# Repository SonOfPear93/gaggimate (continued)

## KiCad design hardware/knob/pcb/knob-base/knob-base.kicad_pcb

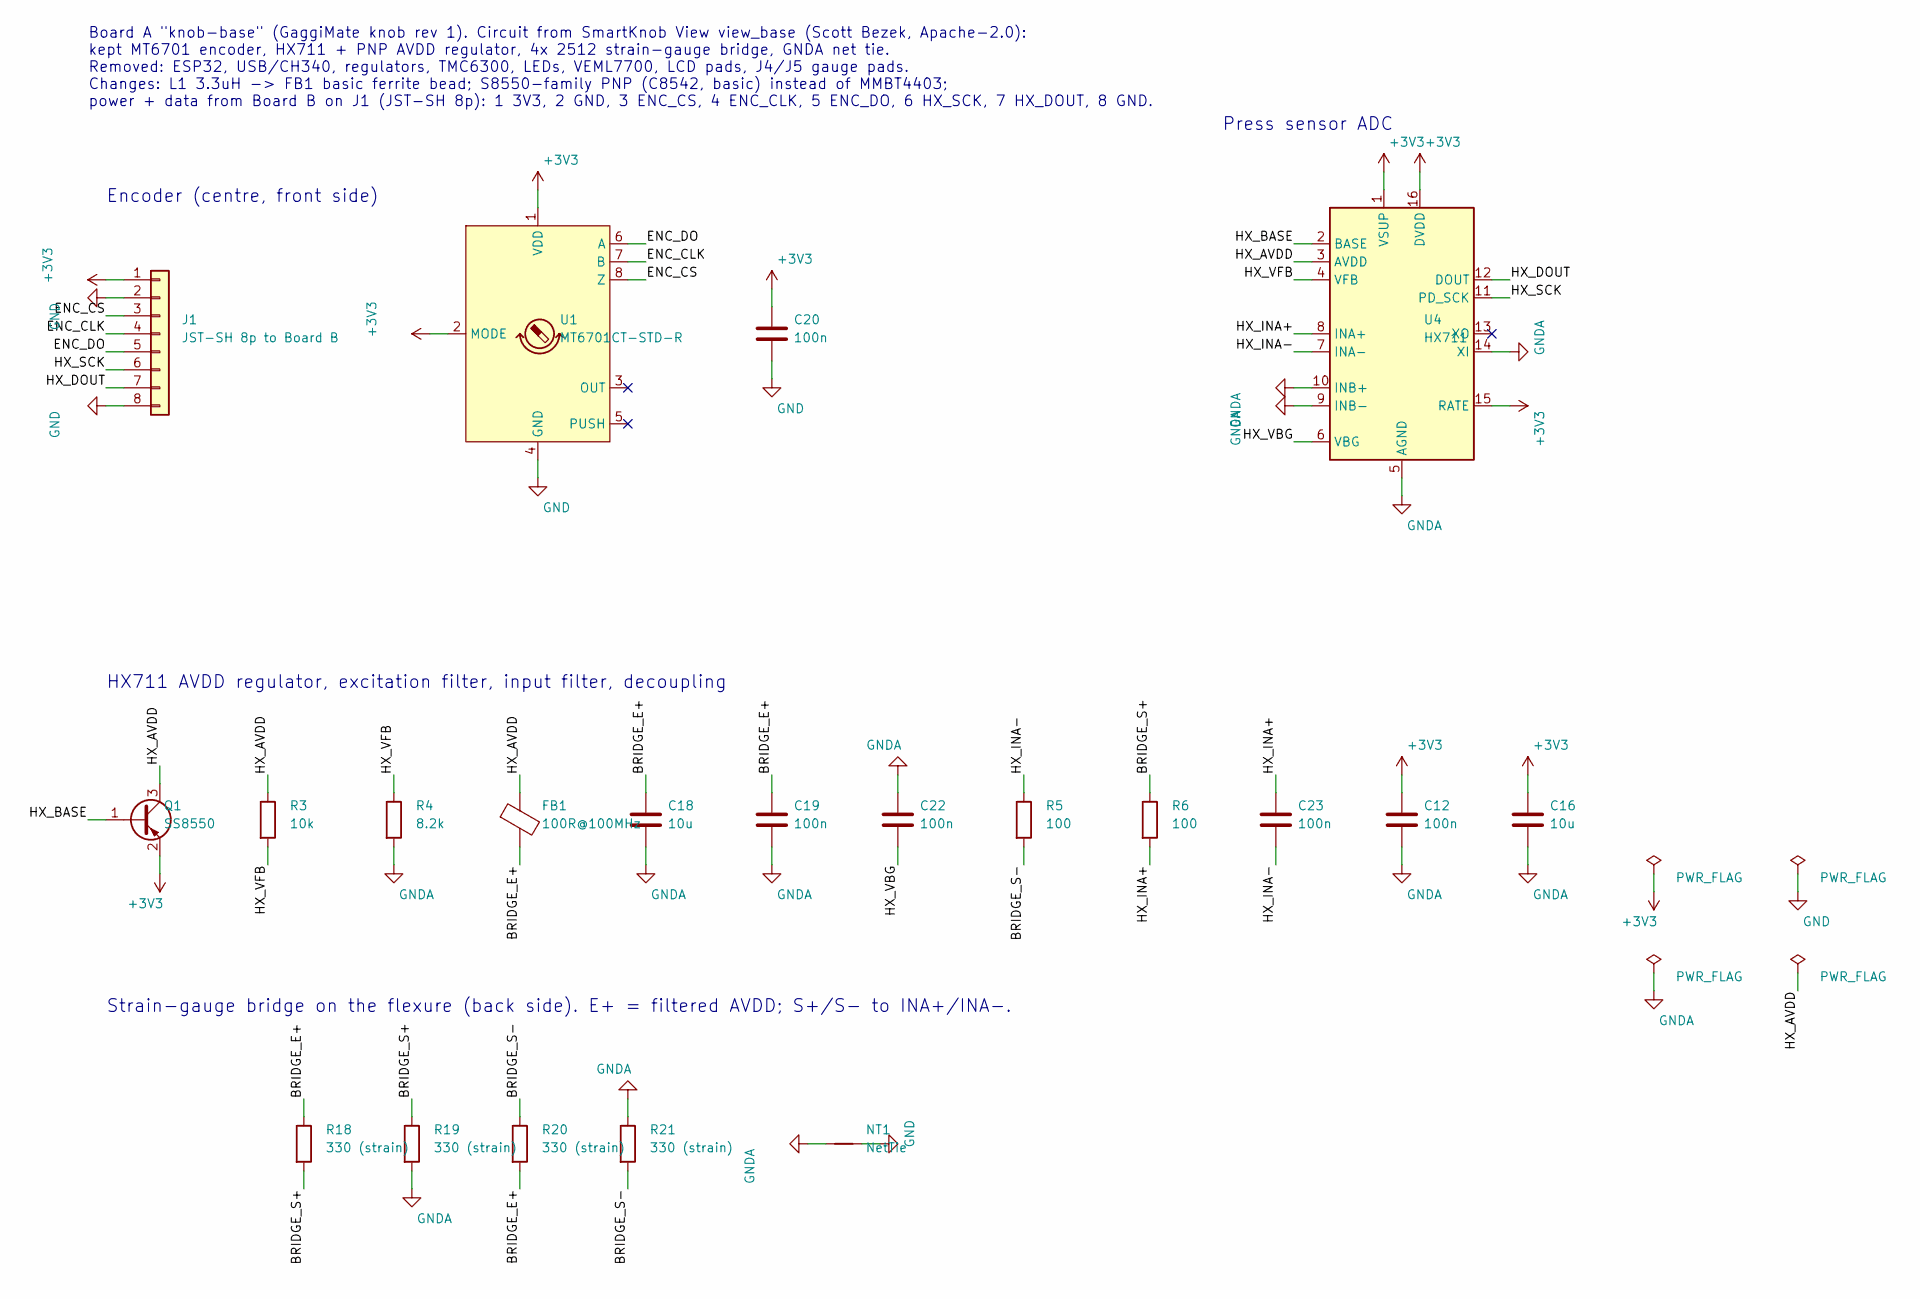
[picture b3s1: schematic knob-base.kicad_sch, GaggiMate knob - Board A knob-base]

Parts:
C12, C19, C20, C22, C23: 100n; C_0603_1608Metric; MPN CC0603KRX7R9BB104; LCSC C14663
C16, C18: 10u; C_0805_2012Metric; MPN CL21A106KAYNNNE; LCSC C15850
FB1: 100R@100MHz; L_0805_2012Metric; MPN GZ2012D101TF; LCSC C1015
J1: JST-SH 8p to Board B; JST_SH_SM08B-SRSS-TB_1x08-1MP_P1.00mm_Horizontal; MPN SM08B-SRSS-TB(LF)(SN); LCSC C160407
NT1: NetTie; NetTie-2_SMD_Pad0.5mm
Q1: SS8550; SOT-23; MPN SS8550 Y2; LCSC C8542
R3: 10k; R_0603_1608Metric; MPN 0603WAF1002T5E; LCSC C25804
R4: 8.2k; R_0603_1608Metric; MPN 0603WAF8201T5E; LCSC C25981
R5, R6: 100; R_0603_1608Metric; MPN 0603WAF1000T5E; LCSC C22775
R18, R19, R20, R21: 330 (strain); R_2512_6332Metric; MPN 25121WJ0331T4E; LCSC C19866
U1: MT6701CT-STD-R; SOIC-8_3.9x4.9mm_P1.27mm; MPN MT6701CT-STD-R; LCSC C3003196
U4: HX711; SOIC-16_3.9x9.9mm_P1.27mm; MPN HX711; LCSC C6705483

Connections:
+3V3: C12.1, C16.1, C20.1, J1.1, Q1.2 (E), U1.1 (VDD), U1.2 (MODE), U4.1 (VSUP), U4.15 (RATE), U4.16 (DVDD)
/BRIDGE_E+: C18.1, C19.1, FB1.2, R18.1, R20.2
/BRIDGE_S+: R6.1, R18.2, R19.1
/BRIDGE_S-: R5.2, R20.1, R21.2
/ENC_CLK: J1.4, U1.7 (B)
/ENC_CS: J1.3, U1.8 (Z)
/ENC_DO: J1.5, U1.6 (A)
/HX_AVDD: FB1.1, Q1.3 (C), R3.1, U4.3 (AVDD)
/HX_BASE: Q1.1 (B), U4.2 (BASE)
/HX_DOUT: J1.7, U4.12 (DOUT)
/HX_INA+: C23.1, R6.2, U4.8 (INA+)
/HX_INA-: C23.2, R5.1, U4.7 (INA-)
/HX_SCK: J1.6, U4.11 (PD_SCK)
/HX_VBG: C22.2, U4.6 (VBG)
/HX_VFB: R3.2, R4.1, U4.4 (VFB)
GND: C20.2, J1.2, J1.8, NT1.2, U1.4 (GND)
GNDA: C12.2, C16.2, C18.2, C19.2, C22.1, NT1.1, R4.2, R19.2, R21.1, U4.5 (AGND), U4.9 (INB-), U4.10 (INB+), U4.14 (XI)

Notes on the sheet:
Board A "knob-base" (GaggiMate knob rev 1). Circuit from SmartKnob View view_base (Scott Bezek, Apache-2.0): kept MT6701 encoder, HX711 + PNP AVDD regulator, 4x 2512 strain-gauge bridge, GNDA net tie. Removed: ESP32, USB/CH340, regulators, TMC6300, LEDs, VEML7700, LCD pads, J4/J5 gauge pads. Change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
Encoder (centre, front side)
Press sensor ADC
HX711 AVDD regulator, excitation filter, input filter, decoupling
Strain-gauge bridge on the flexure (back side). E+ = filtered AVDD; S+/S- to INA+/INA-.

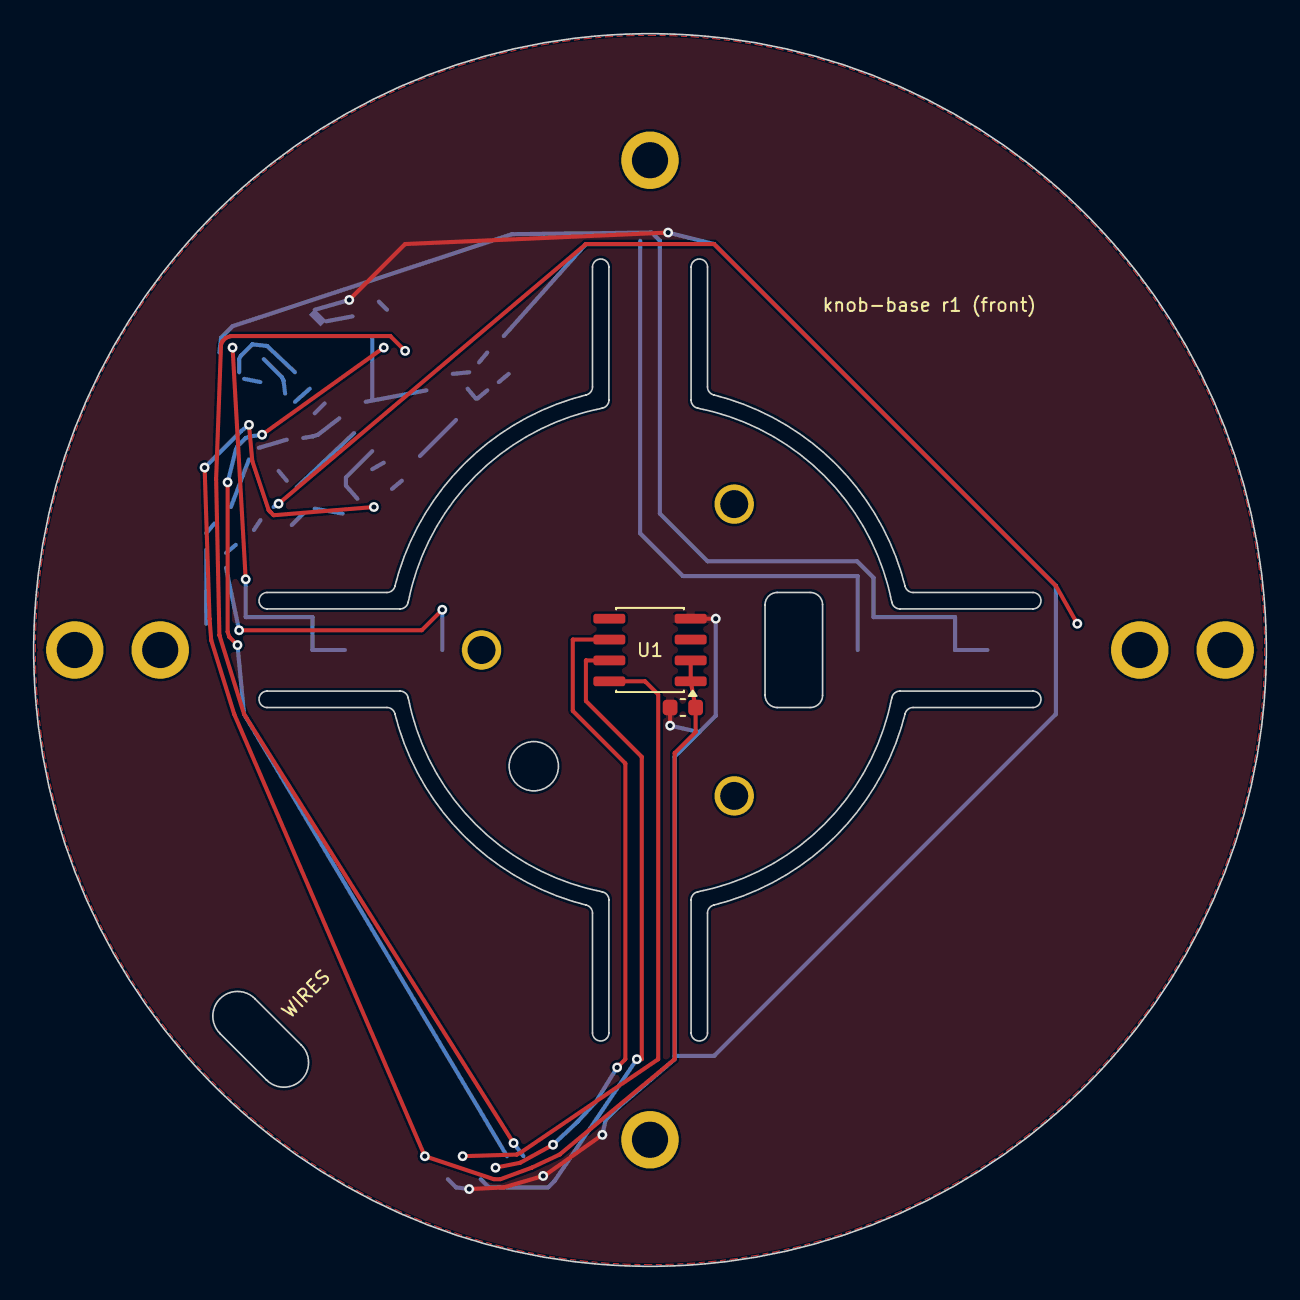
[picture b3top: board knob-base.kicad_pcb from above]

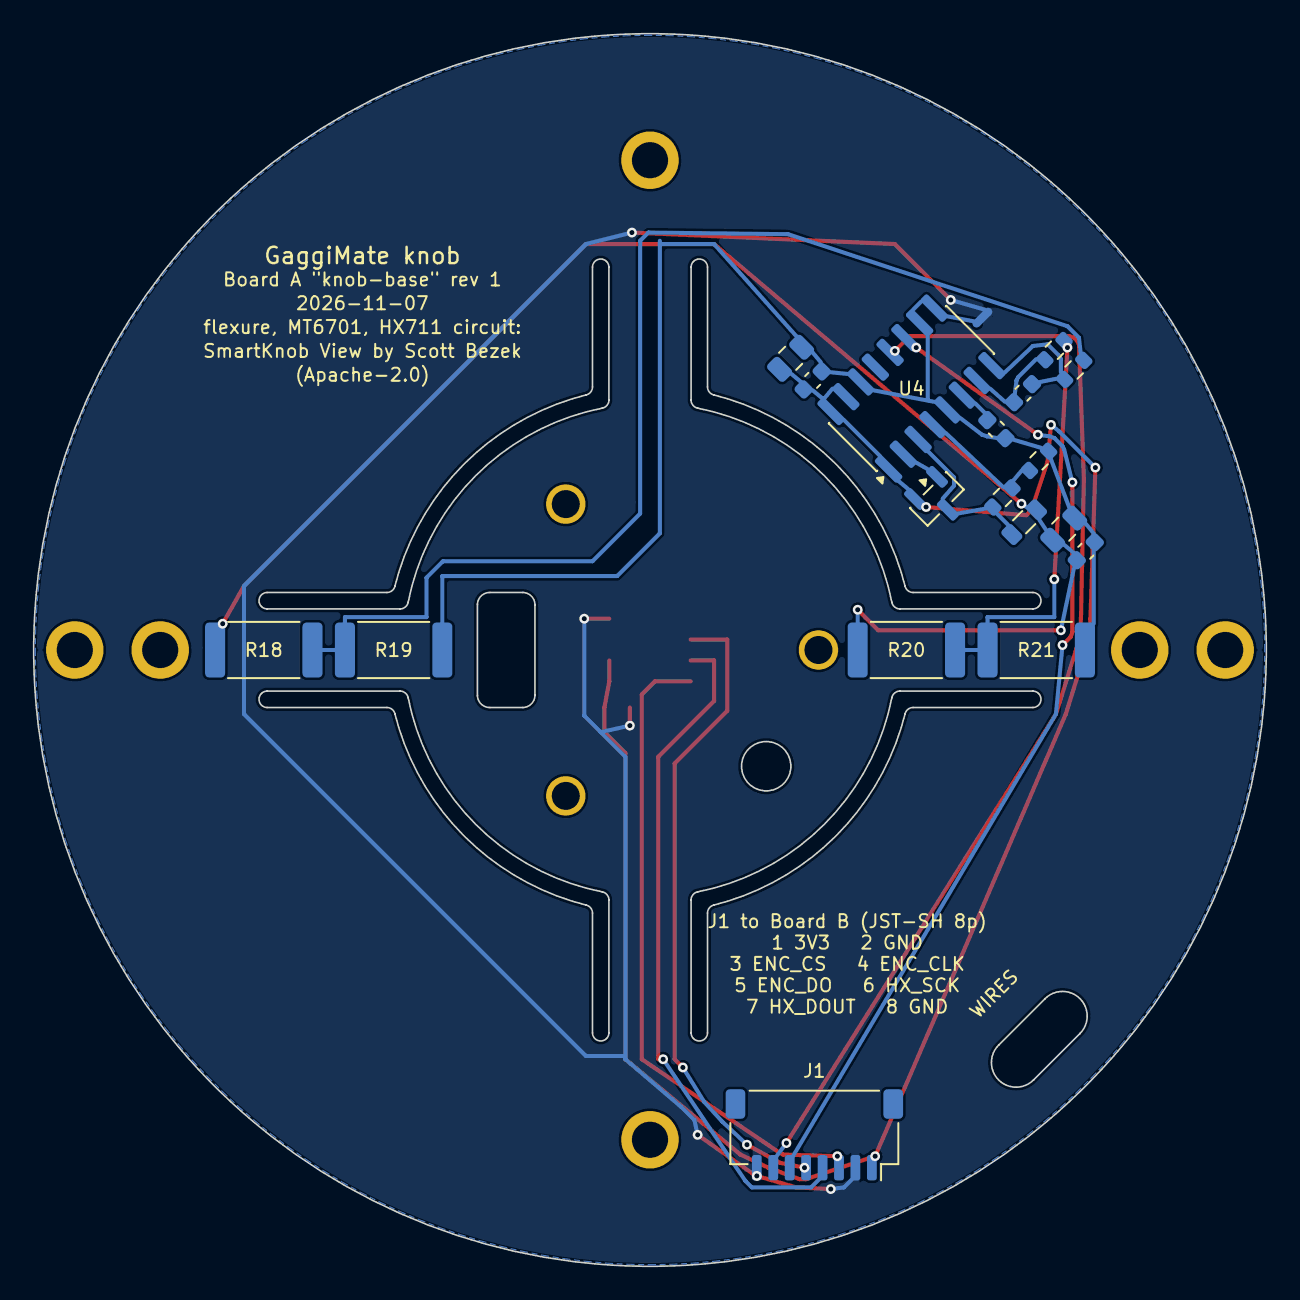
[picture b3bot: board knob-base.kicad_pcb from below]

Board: 2 copper layers, 75.0 x 75.0 mm, 30 parts (19 on the bottom side), 17 nets.

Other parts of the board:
H1, H2, H3: M1.6 motor; MountingHole_M1.6
H4, H5, H6, H7: M2 mount; MountingHole_2.2mm_M2_ISO7380_Pad_NonVirtual
H8, H9: D2.2 align; MountingHole_2.2mm_M2_ISO7380_Pad_NonVirtual

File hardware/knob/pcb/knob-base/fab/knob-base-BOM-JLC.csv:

Comment,Designator,Footprint,LCSC Part #
100n,"C12,C19,C20,C22,C23",C_0603_1608Metric,C14663
10u,"C16,C18",C_0805_2012Metric,C15850
100R@100MHz,FB1,L_0805_2012Metric,C1015
JST-SH 8p to Board B,J1,JST_SH_SM08B-SRSS-TB_1x08-1MP_P1.00mm_Horizontal,C160407
SS8550,Q1,SOT-23,C8542
10k,R3,R_0603_1608Metric,C25804
8.2k,R4,R_0603_1608Metric,C25981
100,"R5,R6",R_0603_1608Metric,C22775
330 (strain),"R18,R19,R20,R21",R_2512_6332Metric,C19866
MT6701CT-STD-R,U1,SOIC-8_3.9x4.9mm_P1.27mm,C3003196
HX711,U4,SOIC-16_3.9x9.9mm_P1.27mm,C6705483

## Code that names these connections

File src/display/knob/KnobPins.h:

// GPIO map of the GaggiMate Knob main board ("knob-main", ESP32-S3-WROOM-1-N16R8).
// Source of truth: docs/superpowers/specs/2026-11-07-smartknob-input-design.md §5.
// If the hardware map changes, update that table, this header and
// KNOB_AMOLED_175_HW_CONFIG (drivers/AmoledDisplay/pin_config.h) together.
#pragma once

#include <cstdint>

namespace knob::pins {

// DRV8311H motor driver, 3x PWM mode (INHx = PWM, all INLx tied to DRV_EN).
constexpr int8_t DRV_SOA = 1;     // current-sense out A (ADC1), unused in rev 1
constexpr int8_t DRV_SOB = 2;     // current-sense out B (ADC1), unused in rev 1
constexpr int8_t DRV_NFAULT = 3;  // input, active low, 10 k pull-up (strapping pin, input only)
constexpr int8_t DRV_INHA = 4;    // PWM phase A
constexpr int8_t DRV_INHB = 5;    // PWM phase B
constexpr int8_t DRV_INHC = 18;   // PWM phase C
constexpr int8_t DRV_NSLEEP = 21; // high = driver awake (100 k pull-down)
constexpr int8_t DRV_EN = 47;     // drives all three INLx (enable / Hi-Z)

// Touch controller (CST9217 @ 0x5A), optional.
constexpr int8_t TP_SCL = 6;
constexpr int8_t TP_SDA = 7;
constexpr int8_t TP_RST = 8;
constexpr int8_t TP_INT = 9;

// 1.75" CO5300 AMOLED over QSPI.
constexpr int8_t LCD_CS = 10;
constexpr int8_t LCD_D0 = 11;
constexpr int8_t LCD_CLK = 12;
constexpr int8_t LCD_D1 = 13;
constexpr int8_t LCD_D2 = 14;
constexpr int8_t LCD_D3 = 15;
constexpr int8_t LCD_RST = 16;
constexpr int8_t LCD_EN = 17; // high = panel power on (load switch on board B)

// MT6701 magnetic encoder, SSI.
constexpr int8_t ENC_CS = 38;
constexpr int8_t ENC_CLK = 39;
constexpr int8_t ENC_DO = 40;

// HX711 strain-gauge ADC.
constexpr int8_t HX_SCK = 41;
constexpr int8_t HX_DOUT = 42;

constexpr int8_t STATUS_LED = 48; // optional single LED
constexpr int8_t BOOT_BUTTON = 0;

} // namespace knob::pins
